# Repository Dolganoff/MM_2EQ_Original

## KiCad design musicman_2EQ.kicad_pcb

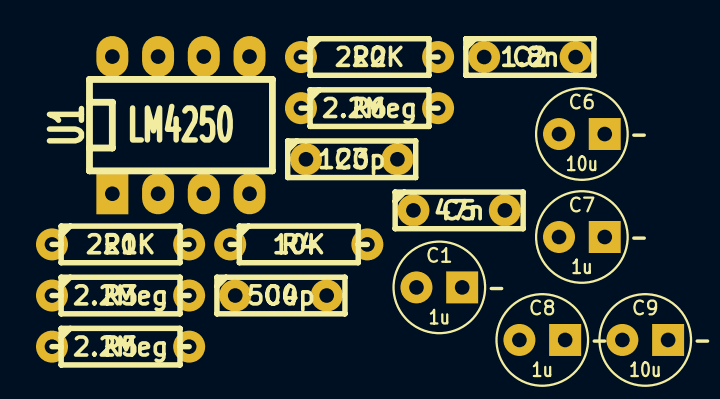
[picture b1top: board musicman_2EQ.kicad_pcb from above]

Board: 2 copper layers, 16 parts (0 on the bottom side), 9 nets, no tracks yet.

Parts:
C1, C7, C8: 1u; C1V5-LARGE_PADS
C2: 1.8n; C2-LARGE_PADS
C3: 120p; C2-LARGE_PADS
C4: 500p; C2-LARGE_PADS
C5: 47n; C2-LARGE_PADS
C6, C9: 10u; C1V5-LARGE_PADS
R1, R2: 220K; R3-LARGE_PADS
R3, R5, R6: 2.2Meg; R3-LARGE_PADS
R4: 10K; R3-LARGE_PADS
U1: LM4250; DIP-8_LARGE_PADS

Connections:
+9V: C8.1, R5.1, U1.7
GND: C7.2, C8.2, C9.2, R3.2, R6.2, U1.4
unnamed: C1.1, C2.2, R1.2
unnamed: C3.1, C4.1, C5.1, C6.1, U1.6
unnamed: C3.2, R1.1, R2.2, U1.2
unnamed: C5.2, R2.1, R4.1
unnamed: C9.1, R4.2
unnamed: R3.1, U1.8
ref: C7.1, R5.2, R6.1, U1.3

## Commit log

2014-10-23 :space_invader: Added .gitattributes
2014-10-23 initial
2014-10-24 board routed
2014-10-24 reorg dossiers
2014-10-25 board changes, gbr generation
2014-10-31 autosave
2014-11-01 01/11/2014 minor changes
